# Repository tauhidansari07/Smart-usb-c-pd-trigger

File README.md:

# Smart USB-C Power Delivery (PD) Trigger Board

A compact, low-cost USB-C Power Delivery decoy and utility bench tool. This project allows you to cycle through standard USB-PD profiles (5V, 9V, 12V, 15V, and 20V) at the push of a single button using a standard USB-C wall adapter or power bank.

Unlike basic decoy boards, this design features an active closed-loop feedback mechanism to monitor the actual voltage output, ensuring the status indicators always display accurate readings even if a charger has limited power profiles.

## Features

- **Single-Button Cycling:** Effortlessly step through 5V, 9V, 12V, 15V, and 20V target profiles using a single debounced tactile switch.
- **Closed-Loop LED Feedback:** An internal ADC reads the negotiated voltage through a resistor divider. The corresponding LED illuminates based on the *actual* output voltage, preventing false indicators if a charger defaults to a lower fallback voltage.
- **Ultra Low-Cost Architecture:** Built using the 32-bit RISC-V CH32V003 microcontroller and a dedicated WCH CH224K USB-PD sink controller.
- **Hardware Protection:** Equipped with a wide-input linear regulator (LDO) rated up to 30V to safeguard logic components against high-voltage transients during 20V switching.

## Hardware Specifications

- **Microcontroller:** WCH CH32V003F4P6 (TSSOP-20)
- **PD Controller:** WCH CH224K (ESSOP-10)
- **LDO Regulator:** Holtek HT7533-1 (SOT-89, 30V Max Input, 3.3V Output)
- **Voltage Sensing:** 100kΩ / 15kΩ resistor divider routed to ADC Channel 7 (`PD4`)
- **Programming Interface:** 1-Wire Serial Debug Interface (SDI) breakout header for WCH-LinkE

## Repository Structure

- `/firmware` : C source code matching standard peripheral libraries (MounRiver Studio / PlatformIO).
- `/hardware` : KiCad schematic and PCB layout design files.

-

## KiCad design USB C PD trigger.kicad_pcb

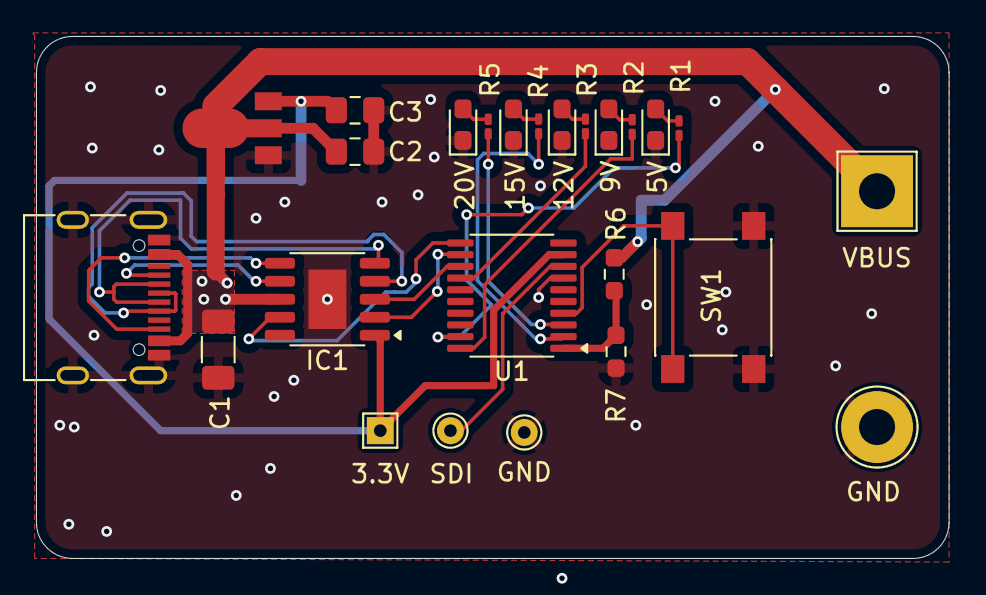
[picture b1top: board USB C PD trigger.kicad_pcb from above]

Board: 2 copper layers, 50.7 x 29.0 mm, 25 parts (0 on the bottom side), 24 nets.

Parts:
C1: 10u; C_1206_3216Metric_Pad1.33x1.80mm_HandSolder
C2: 1u; C_0805_2012Metric_Pad1.18x1.45mm_HandSolder
C3: 10u; C_0805_2012Metric_Pad1.18x1.45mm_HandSolder
D1: 5V; LED_0603_1608Metric_Pad1.05x0.95mm_HandSolder
D2: 9V; LED_0603_1608Metric_Pad1.05x0.95mm_HandSolder
D3: 12V; LED_0603_1608Metric_Pad1.05x0.95mm_HandSolder
D4: 15V; LED_0603_1608Metric_Pad1.05x0.95mm_HandSolder
D5: 20V; LED_0603_1608Metric_Pad1.05x0.95mm_HandSolder
IC1: CH224K; SSOP-10-1EP_3.9x4.9mm_P1mm_EP2.1x3.3mm
J1: USB_C_Receptacle_USB2.0_16P; USB_C_Receptacle_G-Switch_GT-USB-7010ASV
R1, R2, R3, R4, R5: 1K; R_0201_0603Metric_Pad0.64x0.40mm_HandSolder
R6: 100K; R_0603_1608Metric_Pad0.98x0.95mm_HandSolder
R7: 15K; R_0603_1608Metric_Pad0.98x0.95mm_HandSolder
SW1: SW_Push; SW_Push_1P1T_NO_6x6mm_H9.5mm
TP1: 3.3V; TestPoint_THTPad_1.5x1.5mm_Drill0.7mm
TP2: GND; TestPoint_THTPad_D1.5mm_Drill0.7mm
TP3: SDI; TestPoint_THTPad_D1.5mm_Drill0.7mm
TP4: VBUS; TestPoint_THTPad_4.0x4.0mm_Drill2.0mm
TP5: GND; TestPoint_THTPad_D4.0mm_Drill2.0mm
U1: CH32V003FxPx; TSSOP-20_4.4x6.5mm_P0.65mm
U2: HT7533-1; SOT89

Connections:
/3V3: C3.2, IC1.1 (VDD), TP1.1, U1.9 (VDD), U2.3 (VO)
/CFG2: IC1.2 (CFG2), U1.12 (PC2)
/CFG3: IC1.3 (CFG3), U1.13 (PC3)
/PC4: R3.2, U1.14 (PC4)
/SDI: TP3.1, U1.8 (PD0)
/USB-CC1: IC1.7 (CC1), J1.A5 (CC1)
/USB-CC2: IC1.6 (CC2), J1.B5 (CC2)
/VBUS: C1.1, C2.2, IC1.8 (VBUS), J1.A4 (VBUS), J1.A9 (VBUS), J1.B4 (VBUS), J1.B9 (VBUS), R6.1, TP4.1, U2.2 (VI), U2.2@1 (VI)
GND: C1.2, C2.1, C3.1, D1.1 (K), D2.1 (K), D3.1 (K), D4.1 (K), D5.1 (K), IC1.11 (GND), J1.A1 (GND), J1.A12 (GND), J1.B1 (GND), J1.B12 (GND), J1.S1 (SHIELD), R7.2, SW1.1, TP2.1, TP5.1, U1.7 (VSS), U2.1
unnamed: D1.2 (A), R1.1
unnamed: D2.2 (A), R2.1
unnamed: D3.2 (A), R3.1
unnamed: D4.2 (A), R4.1
unnamed: D5.2 (A), R5.1
unnamed: IC1.9 (CFG1), U1.11 (PC1)
unnamed: IC1.5 (DM), J1.A7 (D-), J1.B7 (D-)
unnamed: IC1.4 (DP), J1.A6 (D+), J1.B6 (D+)
unnamed: J1.A8 (SBU1), J1.B8 (SBU2)
unnamed: R1.2, U1.19 (PD2)
unnamed: R2.2, U1.20 (PD3)
unnamed: R6.2, R7.1, U1.1 (PD4)
unnamed: R4.2, U1.2 (PD5)
unnamed: R5.2, U1.3 (PD6)
unnamed: SW1.2, U1.4 (PD7)

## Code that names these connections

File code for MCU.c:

#include "debug.h"
#include "ch32v00x.h"

/*
 * PIN CONFIGURATION REFERENCE (TSSOP-20):
 * VDD (Pin 6)   -> 3.3V LDO Output
 * VSS (Pin 5)   -> GND Plane
 * PD1 (Pin 3)   -> SWDIO (Programming)
 * PD4 (Pin 17)  -> ADC Input (Center of 100k / 15k Resistor Divider)
 * PC1 (Pin 8)   -> CH224K CFG1
 * PC2 (Pin 9)   -> CH224K CFG2
 * PC3 (Pin 10)  -> CH224K CFG3
 * PD2 (Pin 15)  -> 5V LED (via 1k resistor)
 * PD3 (Pin 16)  -> 9V LED (via 1k resistor)
 * PC4 (Pin 11)  -> 12V LED (via 1k resistor)
 * PD5 (Pin 18)  -> 15V LED (via 1k resistor)
 * PD6 (Pin 19)  -> 20V LED (via 1k resistor)
 * PD7 (Pin 20)  -> Push Button (Active Low, internal Pull-Up)
 */

// Global State tracking
volatile uint8_t requested_state = 0; // 0=5V, 1=9V, 2=12V, 3=15V, 4=20V

// ADC Thresholds for a 100k/15k divider with a 3.3V reference (10-bit ADC: 0-1023)
// 5V input  ≈ 0.65V at pin ≈ ADC value 202 (Threshold: > 280 for 9V)
// 9V input  ≈ 1.17V at pin ≈ ADC value 364 (Threshold: > 420 for 12V)
// 12V input ≈ 1.56V at pin ≈ ADC value 485 (Threshold: > 550 for 15V)
// 15V input ≈ 1.95V at pin ≈ ADC value 606 (Threshold: > 700 for 20V)
// 20V input ≈ 2.60V at pin ≈ ADC value 809

void System_Init(void) {
    GPIO_InitTypeDef GPIO_InitStructure = {0};
    ADC_InitTypeDef ADC_InitStructure = {0};

    // 1. Enable Clocks for Port C, Port D, and ADC1
    RCC_APB2PeriphClockCmd(RCC_APB2Periph_GPIOC | RCC_APB2Periph_GPIOD | RCC_APB2Periph_ADC1, ENABLE);
    
    // Set ADC prescaler (ADCCLK = SYSCLK / 8)
    RCC_ADCCLKConfig(RCC_ADCCLK_Div8);

    // 2. Configure LEDs (PD2, PD3, PD5, PD6) as Push-Pull Outputs
    GPIO_InitStructure.GPIO_Pin = GPIO_Pin_2 | GPIO_Pin_3 | GPIO_Pin_5 | GPIO_Pin_6;
    GPIO_InitStructure.GPIO_Mode = GPIO_Mode_Out_PP;
    GPIO_InitStructure.GPIO_Speed = GPIO_Speed_10MHz;
    GPIO_Init(GPIOD, &GPIO_InitStructure);

    // Configure 12V LED (PC4) as Push-Pull Output
    GPIO_InitStructure.GPIO_Pin = GPIO_Pin_4;
    GPIO_InitStructure.GPIO_Mode = GPIO_Mode_Out_PP;
    GPIO_Init(GPIOC, &GPIO_InitStructure);

    // 3. Configure Button (PD7) as Input with Pull-Up
    GPIO_InitStructure.GPIO_Pin = GPIO_Pin_7;
    GPIO_InitStructure.GPIO_Mode = GPIO_Mode_IPU;
    GPIO_Init(GPIOD, &GPIO_InitStructure);

    // 4. Configure CFG pins (PC1, PC2, PC3) as Push-Pull Outputs initially
    GPIO_InitStructure.GPIO_Pin = GPIO_Pin_1 | GPIO_Pin_2 | GPIO_Pin_3;
    GPIO_InitStructure.GPIO_Mode = GPIO_Mode_Out_PP;
    GPIO_Init(GPIOC, &GPIO_InitStructure);

    // 5. Configure Voltage Sensing Pin (PD4 / AIN7) as Analog Input
    GPIO_InitStructure.GPIO_Pin = GPIO_Pin_4;
    GPIO_InitStructure.GPIO_Mode = GPIO_Mode_AIN;
    GPIO_Init(GPIOD, &GPIO_InitStructure);

    // 6. Initialize ADC1
    ADC_InitStructure.ADC_Mode = ADC_Mode_Independent;
    ADC_InitStructure.ADC_ScanConvMode = DISABLE;
    ADC_InitStructure.ADC_ContinuousConvMode = DISABLE;
    ADC_InitStructure.ADC_ExternalTrigConv = ADC_ExternalTrigConv_None;
    ADC_InitStructure.ADC_DataAlign = ADC_DataAlign_Right;
    ADC_InitStructure.ADC_NbrOfChannel = 1;
    ADC_Init(ADC1, &ADC_InitStructure);

    // Enable ADC1
    ADC_Cmd(ADC1, ENABLE);

    // Calibrate ADC
    ADC_ResetCalibration(ADC1);
    while(ADC_GetResetCalibrationStatus(ADC1));
    ADC_StartCalibration(ADC1);
    while(ADC_GetCalibrationStatus(ADC1));
}

uint16_t Read_Voltage_ADC(void) {
    // Set up Channel 7 (PD4), Sample time 241 cycles
    ADC_RegularChannelConfig(ADC1, ADC_Channel_7, 1, ADC_SampleTime_241Cycles);
    
    // Start conversion
    ADC_SoftwareStartConvCmd(ADC1, ENABLE);
    
    // Wait until conversion is complete
    while(!ADC_GetFlagStatus(ADC1, ADC_FLAG_EOC));
    
    // Return conversion raw 10-bit value
    return ADC_GetConversionValue(ADC1);
}

void Set_PD_Negotiation_Target(uint8_t state) {
    GPIO_InitTypeDef GPIO_InitStructure = {0};

    // Ensure PC1 (CFG1) is returned to Output Mode if coming out of the 20V High-Z state
    if(state != 4) {
        GPIO_InitStructure.GPIO_Pin = GPIO_Pin_1;
        GPIO_InitStructure.GPIO_Mode = GPIO_Mode_Out_PP;
        GPIO_InitStructure.GPIO_Speed = GPIO_Speed_10MHz;
        GPIO_Init(GPIOC, &GPIO_InitStructure);
    }

    // Apply the exact logic table for the WCH CH224K Trigger IC
    switch(state) {
        case 0: // 5V Request (CFG1=0, CFG2=0, CFG3=0)
            GPIO_WriteBit(GPIOC, GPIO_Pin_1, Bit_RESET);
            GPIO_WriteBit(GPIOC, GPIO_Pin_2, Bit_RESET);
            GPIO_WriteBit(GPIOC, GPIO_Pin_3, Bit_RESET);
            break;

        case 1: // 9V Request (CFG1=0, CFG2=0, CFG3=1)
            GPIO_WriteBit(GPIOC, GPIO_Pin_1, Bit_RESET);
            GPIO_WriteBit(GPIOC, GPIO_Pin_2, Bit_RESET);
            GPIO_WriteBit(GPIOC, GPIO_Pin_3, Bit_SET);
            break;

        case 2: // 12V Request (CFG1=0, CFG2=1, CFG3=1)
            GPIO_WriteBit(GPIOC, GPIO_Pin_1, Bit_RESET);
            GPIO_WriteBit(GPIOC, GPIO_Pin_2, Bit_SET);
            GPIO_WriteBit(GPIOC, GPIO_Pin_3, Bit_SET);
            break;

        case 3: // 15V Request (CFG1=1, CFG2=1, CFG3=1)
            GPIO_WriteBit(GPIOC, GPIO_Pin_1, Bit_SET);
            GPIO_WriteBit(GPIOC, GPIO_Pin_2, Bit_SET);
            GPIO_WriteBit(GPIOC, GPIO_Pin_3, Bit_SET);
            break;

        case 4: // 20V Request (CFG1=High-Z, CFG2=0, CFG3=1)
            // Convert PC1 dynamically to Floating Input to create a High-Z state
            GPIO_InitStructure.GPIO_Pin = GPIO_Pin_1;
            GPIO_InitStructure.GPIO_Mode = GPIO_Mode_IN_FLOATING;
            GPIO_Init(GPIOC, &GPIO_InitStructure);
            
            GPIO_WriteBit(GPIOC, GPIO_Pin_2, Bit_RESET);
            GPIO_WriteBit(GPIOC, GPIO_Pin_3, Bit_SET);
            break;
    }
}

void Update_LED_Indicators(void) {
    uint16_t adc_val = Read_Voltage_ADC();
    
    // Clear all status indicators
    GPIO_WriteBit(GPIOD, GPIO_Pin_2 | GPIO_Pin_3 | GPIO_Pin_5 | GPIO_Pin_6, Bit_RESET);
    GPIO_WriteBit(GPIOC, GPIO_Pin_4, Bit_RESET);

    // Map measured ADC thresholds to active status indicator
    if (adc_val > 700) {
        GPIO_WriteBit(GPIOD, GPIO_Pin_6, Bit_SET); // 20V Solid ON
    } 
    else if (adc_val > 550) {
        GPIO_WriteBit(GPIOD, GPIO_Pin_5, Bit_SET); // 15V Solid ON
    } 
    else if (adc_val > 420) {
        GPIO_WriteBit(GPIOC, GPIO_Pin_4, Bit_SET); // 12V Solid ON
    } 
    else if (adc_val > 280) {
        GPIO_WriteBit(GPIOD, GPIO_Pin_3, Bit_SET); // 9V Solid ON
    } 
    else {
        GPIO_WriteBit(GPIOD, GPIO_Pin_2, Bit_SET); // Default 5V Solid ON
    }
}

int main(void) {
    // Core Clock and Driver Init Routines
    NVIC_PriorityGroupConfig(NVIC_PriorityGroup_2);
    SystemCoreClockUpdate();
    Delay_Init();
    System_Init();

    // Default to safest base configuration state (5V) on bootup
    Set_PD_Negotiation_Target(requested_state);

    while(1) {
        // Read Momentary Button (Active Low)
        if(GPIO_ReadInputDataBit(GPIOD, GPIO_Pin_7) == Bit_RESET) {
            
            Delay_Ms(40); // Standard Debounce Window
            
            if(GPIO_ReadInputDataBit(GPIOD, GPIO_Pin_7) == Bit_RESET) {
                
                // Advance targets and cycle back if over bounds
                requested_state++;
                if(requested_state > 4) {
                    requested_state = 0;
                }
                
                // Commit states to CFG pins to trigger the CH224K handshake
                Set_PD_Negotiation_Target(requested_state);
                
                // Lock execution here until user completely releases the physical button
                while(GPIO_ReadInputDataBit(GPIOD, GPIO_Pin_7) == Bit_RESET) {
                    Delay_Ms(10);
                }
            }
        }
        
        // Execute closed-loop system checks and update outputs dynamically
        Update_LED_Indicators();
        Delay_Ms(100); 
    }
}
